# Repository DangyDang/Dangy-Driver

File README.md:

A DC motor driver board built around an Artery AT32F423CBT7 MCU. It drives a single brushed DC motor through an H-bridge of four
100 V N-channel MOSFETs, measures the current in each half-bridge with shunt resistors and op-amps, and talks over CAN and UART.
Quadrature encoder feedback is supported.

The driver should work fine with 4s lipo batt. If you want to use 3s, bridge the 12V regulator.

THE PROJECT IS STILL UNDER DEVELOPMENT.
I'll try to upload the firmware asap.

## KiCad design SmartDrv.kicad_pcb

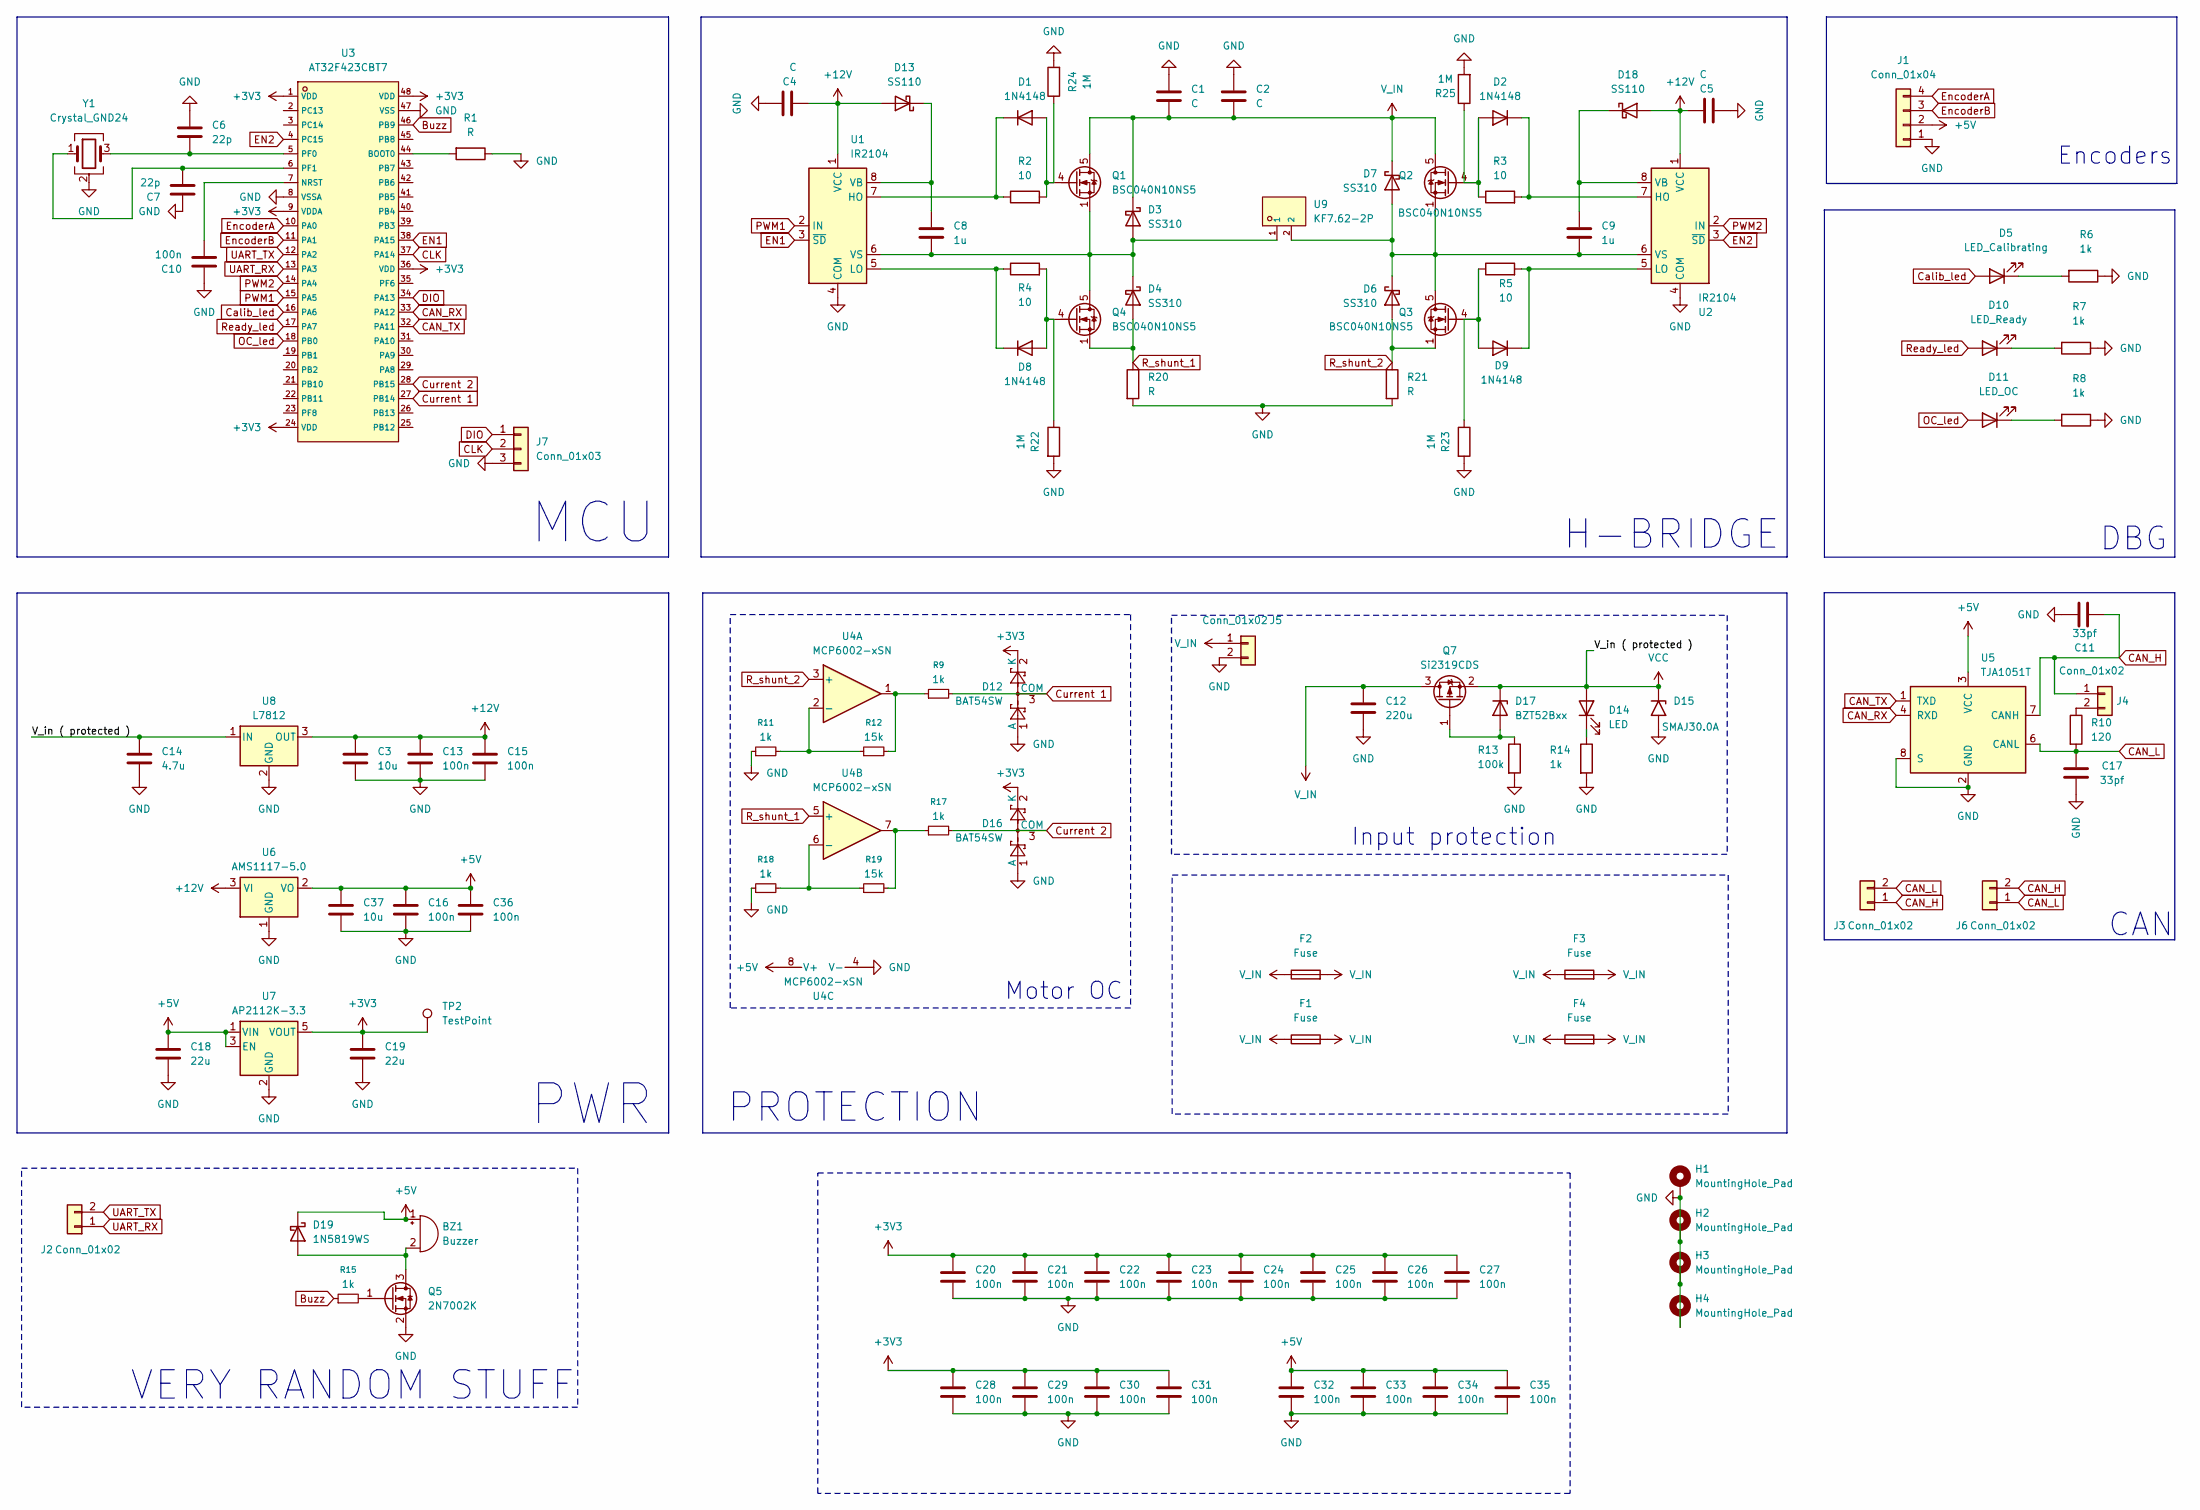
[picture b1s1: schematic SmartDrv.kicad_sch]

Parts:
BZ1: Buzzer; PUIAudio_SMT_0825_S_4_R
C1, C2: C; CP_Elec_8x10
C3, C37: 10u; C_0805_2012Metric
C4, C5: C; C_0805_2012Metric
C6, C7: 22p; C_0603_1608Metric
C8, C9: 1u; C_0805_2012Metric
C10, C20, C21, C22, C23, C24, C25, C26, C27, C28, C29, C30, C31, C32, C33, C34, C35: 100n; C_0603_1608Metric
C11, C17: 33pf; C_0603_1608Metric
C12: 220u; CP_Elec_8x10
C13, C15, C16, C36: 100n; C_0805_2012Metric
C14: 4.7u; C_1210_3225Metric
C18, C19: 22u; C_0805_2012Metric
D1, D2, D8, D9: 1N4148; D_SOD-323
D3, D4, D6, D7: SS310; D_SMA
D5: LED_Calibrating; LED_0805_2012Metric
D10: LED_Ready; LED_0805_2012Metric
D11: LED_OC; LED_0805_2012Metric
D12, D16: BAT54SW; SOT-323_SC-70
D13, D18: SS110; D_SMA
D14: LED; LED_0805_2012Metric
D15: SMAJ30.0A; D_SMA
D17: BZT52Bxx; D_SOD-123F
D19: 1N5819WS; D_SOD-323
F1, F2, F3, F4: Fuse; Fuse_1812_4532Metric
H1, H2, H3, H4: MountingHole_Pad; MountingHole_2.5mm_Pad_Via
J1: Conn_01x04; JST_EH_B4B-EH-A_1x04_P2.50mm_Vertical
J2, J3, J6: Conn_01x02; JST_EH_B2B-EH-A_1x02_P2.50mm_Vertical
J4: Conn_01x02; PinHeader_1x02_P2.54mm_Vertical
J5: Conn_01x02; TerminalBlock_MaiXu_MX126-5.0-02P_1x02_P5.00mm
J7: Conn_01x03; PinHeader_1x03_P2.54mm_Vertical
Q1, Q2, Q3, Q4: BSC040N10NS5; TDSON-8-1
Q5: 2N7002K; SOT-23
Q7: Si2319CDS; SOT-23
R1: R; R_0805_2012Metric
R2, R3, R4, R5: 10; R_0805_2012Metric
R6, R7, R8, R9, R11, R14, R15, R17, R18: 1k; R_0805_2012Metric
R10: 120; R_0805_2012Metric
R12, R19: 15k; R_0805_2012Metric
R13: 100k; R_0805_2012Metric
R20, R21: R; R_2512_6332Metric
R22, R23, R24, R25: 1M; R_0805_2012Metric
TP2: TestPoint; TestPoint_Pad_D1.0mm
U1, U2: IR2104; HSOP-8-1EP_3.9x4.9mm_P1.27mm_EP2.3x2.3mm
U3: AT32F423CBT7; C6705024_LQFP-48_L7_0-W7_0-P0_50-LS9_0-BL; LCSC C6705024
U4: MCP6002-xSN; SOIC-8_3.9x4.9mm_P1.27mm
U5: TJA1051T; SOIC-8_3.9x4.9mm_P1.27mm
U6: AMS1117-5.0; SOT-223-3_TabPin2
U7: AP2112K-3.3; SOT-23-5
U8: L7812; TO-252-2
U9: KF7.62-2P; C707824_CONN-TH_KF7_62-2P; LCSC C707824
Y1: Crystal_GND24; Crystal_SMD_3225-4Pin_3.2x2.5mm

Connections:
+3V3: C19.1, C20.1, C21.1, C22.1, C23.1, C24.1, C25.1, C26.1, C27.1, C28.1, C29.1, C30.1, C31.1, D12.2 (K), D16.2 (K), TP2.1, U3.1 (VDD), U3.9 (VDDA), U3.24 (VDD), U3.36 (VDD), U3.48 (VDD), U7.5 (VOUT)
+5V: BZ1.1 (+), C16.1, C18.1, C32.1, C33.1, C34.1, C35.1, C36.1, C37.1, D19.1 (K), J1.2, U4.8 (V+), U5.3 (VCC), U6.2 (VO), U7.1 (VIN), U7.3 (EN); also elsewhere on the board
+12V: C3.1, C4.2, C5.2, C13.1, C15.1, D13.2 (A), D18.2 (A), U1.1 (VCC), U2.1 (VCC), U6.3 (VI), U8.3 (OUT)
Buzz: R15.1, U3.46 (PB9)
CAN_H: C11.1, J3.1, J4.1, J6.2, U5.7 (CANH)
CAN_L: C17.1, J3.2, J6.1, R10.2, U5.6 (CANL)
CAN_RX: U3.33 (PA12), U5.4 (RXD)
CAN_TX: U3.32 (PA11), U5.1 (TXD)
CLK: J7.2, U3.37 (PA14)
Calib_led: D5.2 (A), U3.16 (PA6)
Current 1: D12.3 (COM), R9.2, U3.27 (PB14)
Current 2: D16.3 (COM), R17.2, U3.28 (PB15)
DIO: J7.1, U3.34 (PA13)
EN1: U1.3 (~SD), U3.38 (PA15)
EN2: U2.3 (~SD), U3.4 (PC15)
EncoderA: J1.4, U3.10 (PA0)
EncoderB: J1.3, U3.11 (PA1)
GND: C1.1, C2.1, C3.2, C4.1, C5.1, C6.1, C7.1, C10.1, C11.2, C12.2, C13.2, C14.2, C15.2, C16.2, C17.2, C18.2, C19.2, C20.2, C21.2, C22.2, C23.2, C24.2, C25.2, C26.2, C27.2, C28.2, C29.2, C30.2, C31.2, C32.2, C33.2, C34.2, C35.2, C36.2, C37.2, D12.1 (A), D15.2 (A2), D16.1 (A), H1.1, H2.1, H3.1, H4.1, J1.1, J5.2, J7.3, Q5.2 (S), R1.1, R6.1, R7.1, R8.1, R11.1, R13.2, R14.2, R18.1, R20.2, R21.2, R22.2, R23.2, R24.2, R25.2, U1.4 (COM), U2.4 (COM), U3.8 (VSSA), U3.47 (VSS), U4.4 (V-), U5.2 (GND), U5.8 (S), U6.1 (GND), U7.2 (GND), U8.2 (GND), Y1.2 (G), Y1.4 (G)
unnamed: BZ1.2 (-), D19.2 (A), Q5.3 (D)
unnamed: D1.2 (A), Q1.4 (G), R2.2, R24.1
unnamed: D1.1 (K), R2.1, U1.7 (HO)
unnamed: D2.2 (A), Q2.4 (G), R3.1, R25.1
unnamed: D2.1 (K), R3.2, U2.7 (HO)
unnamed: C8.2, D3.2 (A), D4.1 (K), Q1.1 (S), Q1.2 (S), Q1.3 (S), Q4.5 (D), U1.6 (VS), U9.1
unnamed: D5.1 (K), R6.2
unnamed: C9.2, D6.1 (K), D7.2 (A), Q2.1 (S), Q2.2 (S), Q2.3 (S), Q3.5 (D), U2.6 (VS), U9.2
unnamed: D8.2 (A), Q4.4 (G), R4.2, R22.1
unnamed: D8.1 (K), R4.1, U1.5 (LO)
unnamed: D9.2 (A), Q3.4 (G), R5.1, R23.1
unnamed: D9.1 (K), R5.2, U2.5 (LO)
unnamed: D10.1 (K), R7.2
unnamed: D11.1 (K), R8.2
unnamed: C8.1, D13.1 (K), U1.8 (VB)
unnamed: D14.1 (K), R14.1
unnamed: D17.2 (A), Q7.1 (G), R13.1
unnamed: C9.1, D18.1 (K), U2.8 (VB)
unnamed: J4.2, R10.1
unnamed: Q5.1 (G), R15.2
unnamed: R9.1, R12.2, U4.1
unnamed: R17.1, R19.2, U4.7
unnamed: R1.2, U3.44 (BOOT0)
unnamed: C10.2, U3.7 (NRST)
unnamed: C6.2, U3.5 (PF0), Y1.3
unnamed: C7.2, U3.6 (PF1), Y1.1
unnamed: R11.2, R12.1, U4.2 (-)
unnamed: R18.2, R19.1, U4.6 (-)
OC_led: D11.2 (A), U3.18 (PB0)
PWM1: U1.2 (IN), U3.15 (PA5)
PWM2: U2.2 (IN), U3.14 (PA4)
R_shunt_1: D4.2 (A), Q4.1 (S), Q4.2 (S), Q4.3 (S), R20.1, U4.5 (+)
R_shunt_2: D6.2 (A), Q3.1 (S), Q3.2 (S), Q3.3 (S), R21.1, U4.3 (+)
Ready_led: D10.2 (A), U3.17 (PA7)
UART_RX: J2.1, U3.13 (PA3)
UART_TX: J2.2, U3.12 (PA2)
VCC: C14.1, D14.2 (A), D15.1 (A1), D17.1 (K), Q7.2 (S), U8.1 (IN)
V_IN: C1.2, C2.2, C12.1, D3.1 (K), D7.1 (K), F1.1, F1.2, F2.1, F2.2, F3.1, F3.2, F4.1, F4.2, J5.1, Q1.5 (D), Q2.5 (D), Q7.3 (D)

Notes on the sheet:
CAN
VERY RANDOM STUFF
H-BRIDGE
MCU
PROTECTION
Encoders
DBG
Motor OC
PWR
Input protection

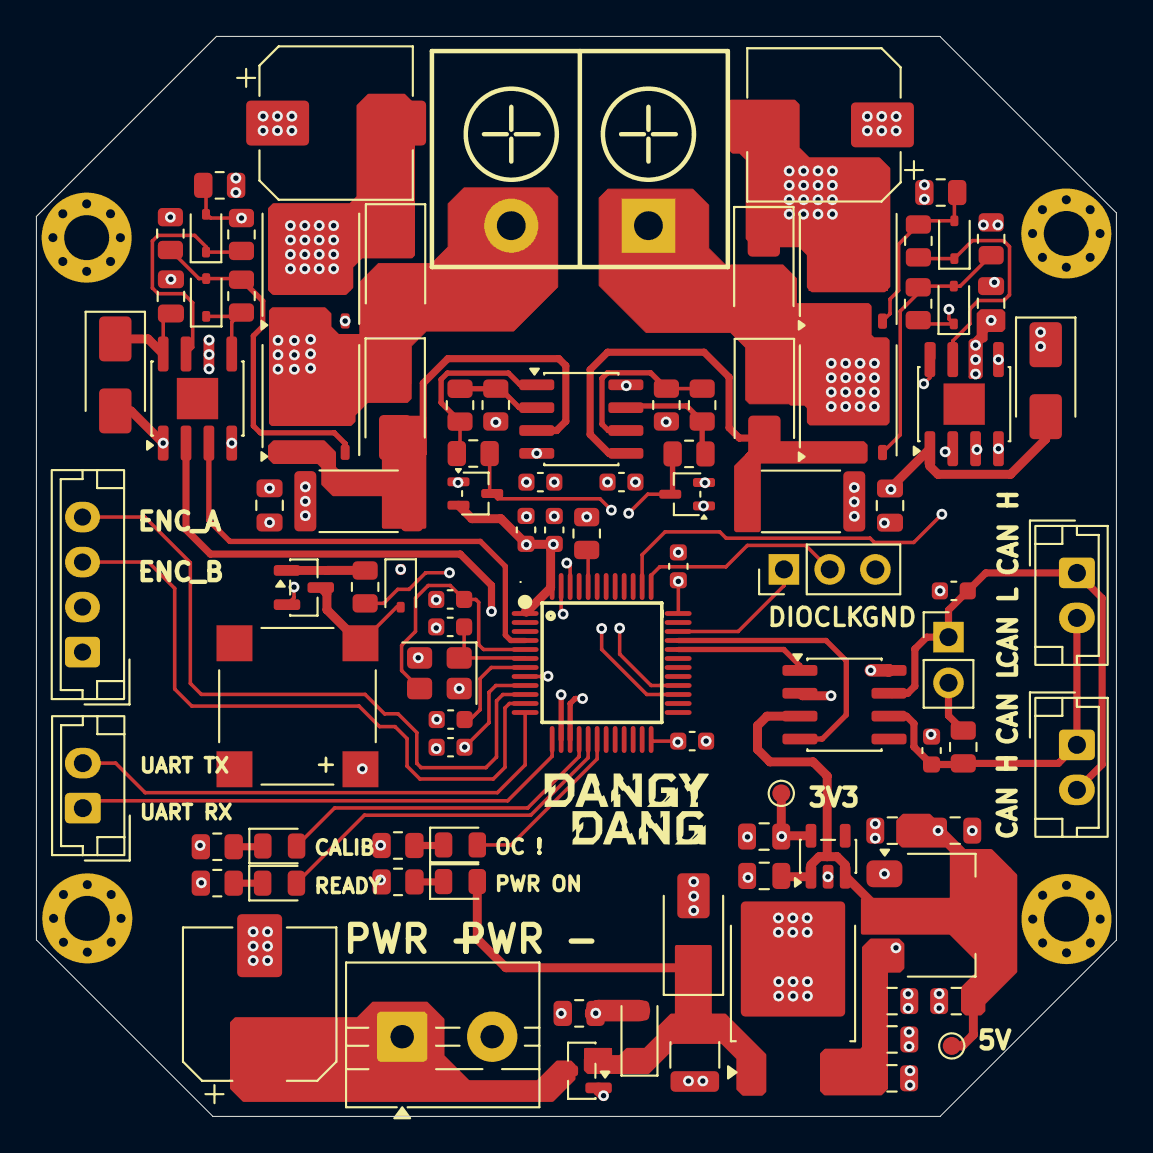
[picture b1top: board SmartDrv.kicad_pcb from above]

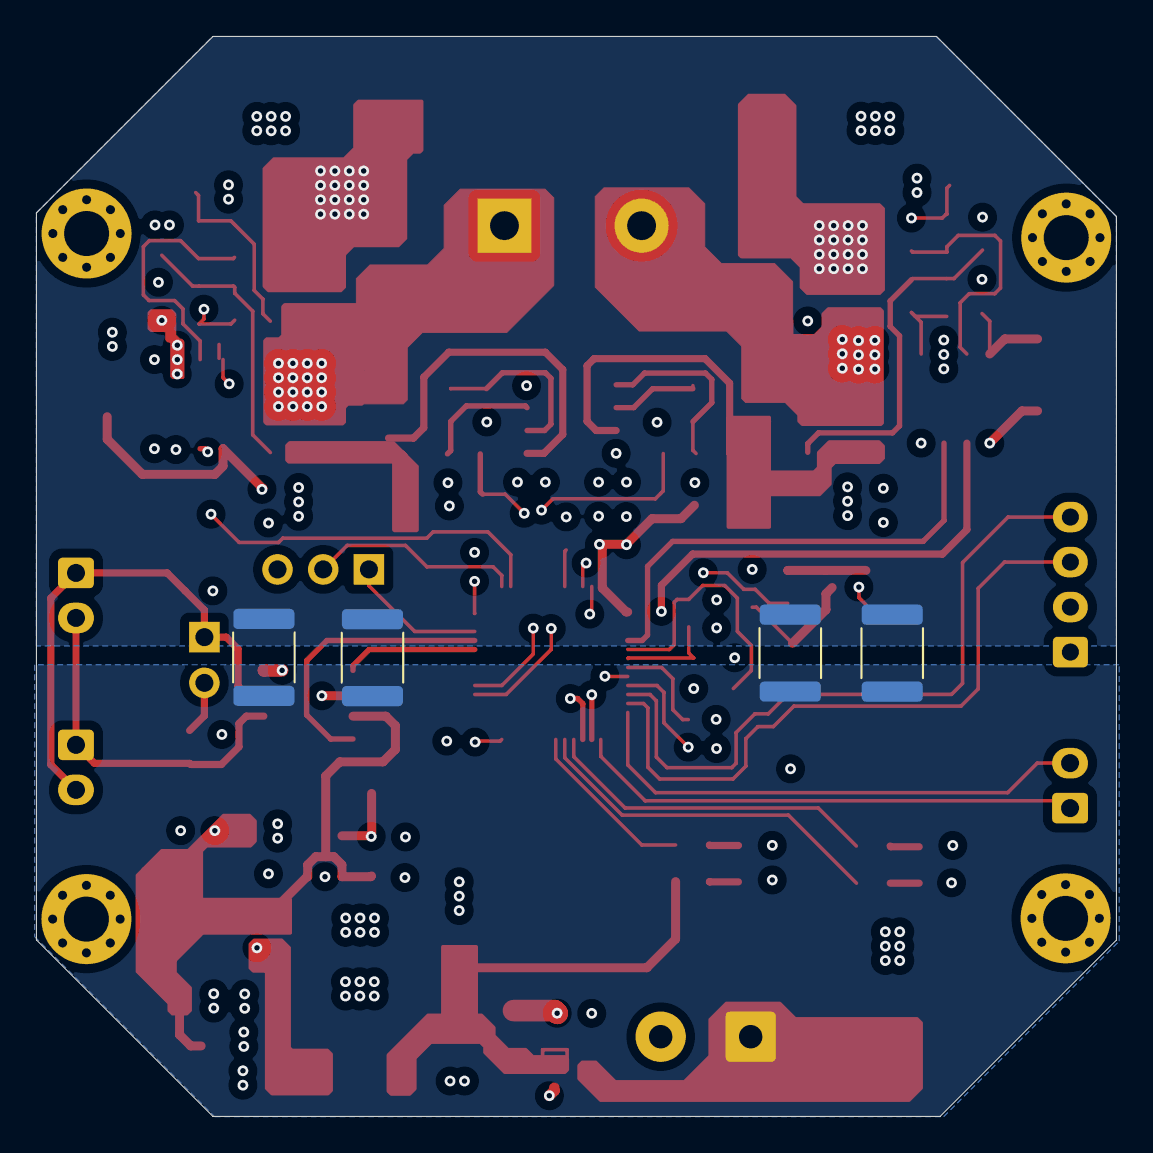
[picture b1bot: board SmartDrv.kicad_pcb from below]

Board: 4 copper layers, 60.0 x 60.0 mm, 105 parts (4 on the bottom side), 56 nets.

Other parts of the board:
TP1: TestPoint; TestPoint_Pad_D1.0mm

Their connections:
+5V: TP1.1; also elsewhere on the board
